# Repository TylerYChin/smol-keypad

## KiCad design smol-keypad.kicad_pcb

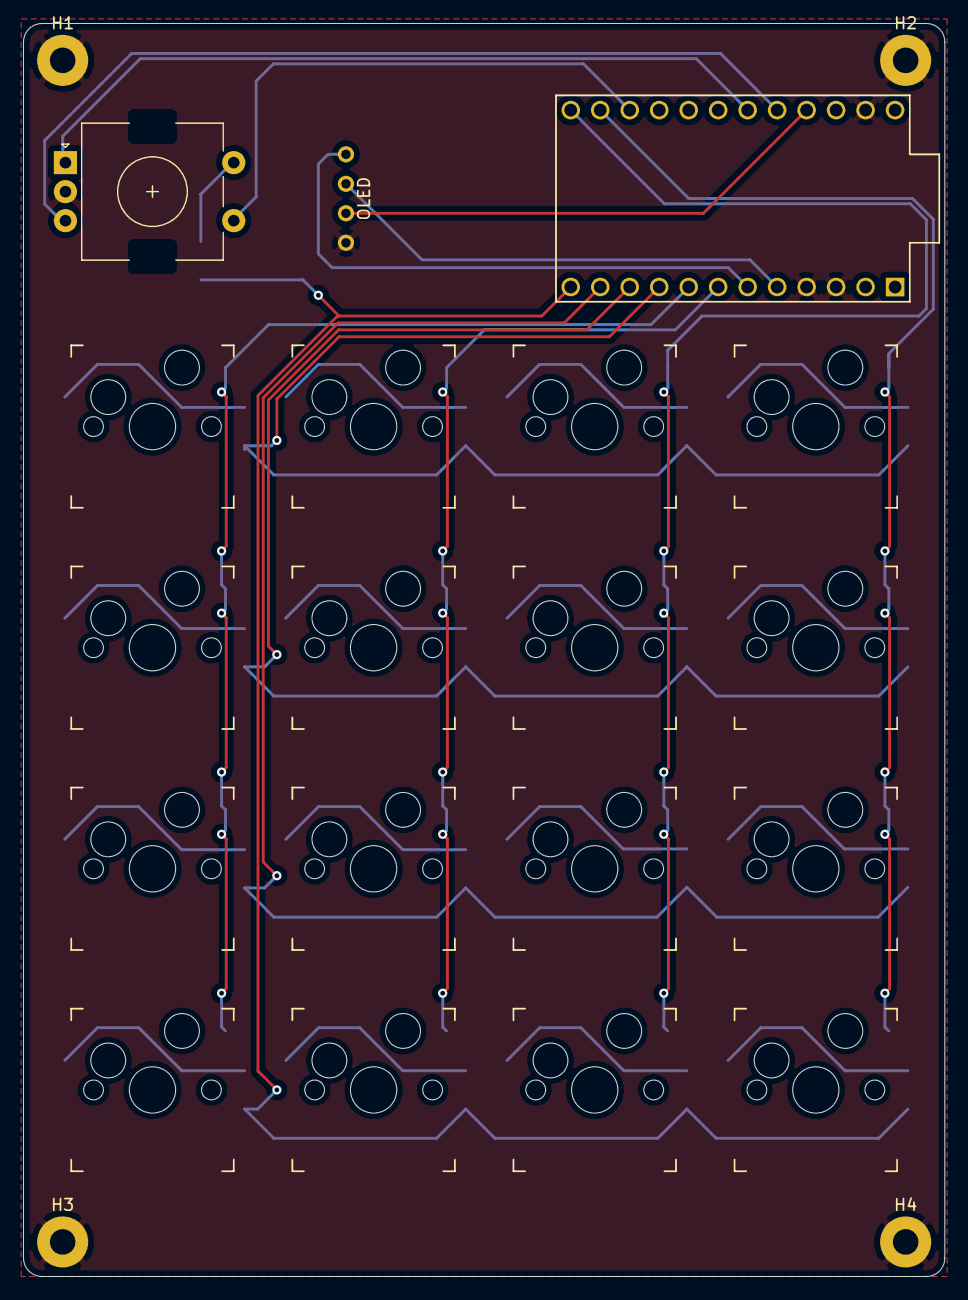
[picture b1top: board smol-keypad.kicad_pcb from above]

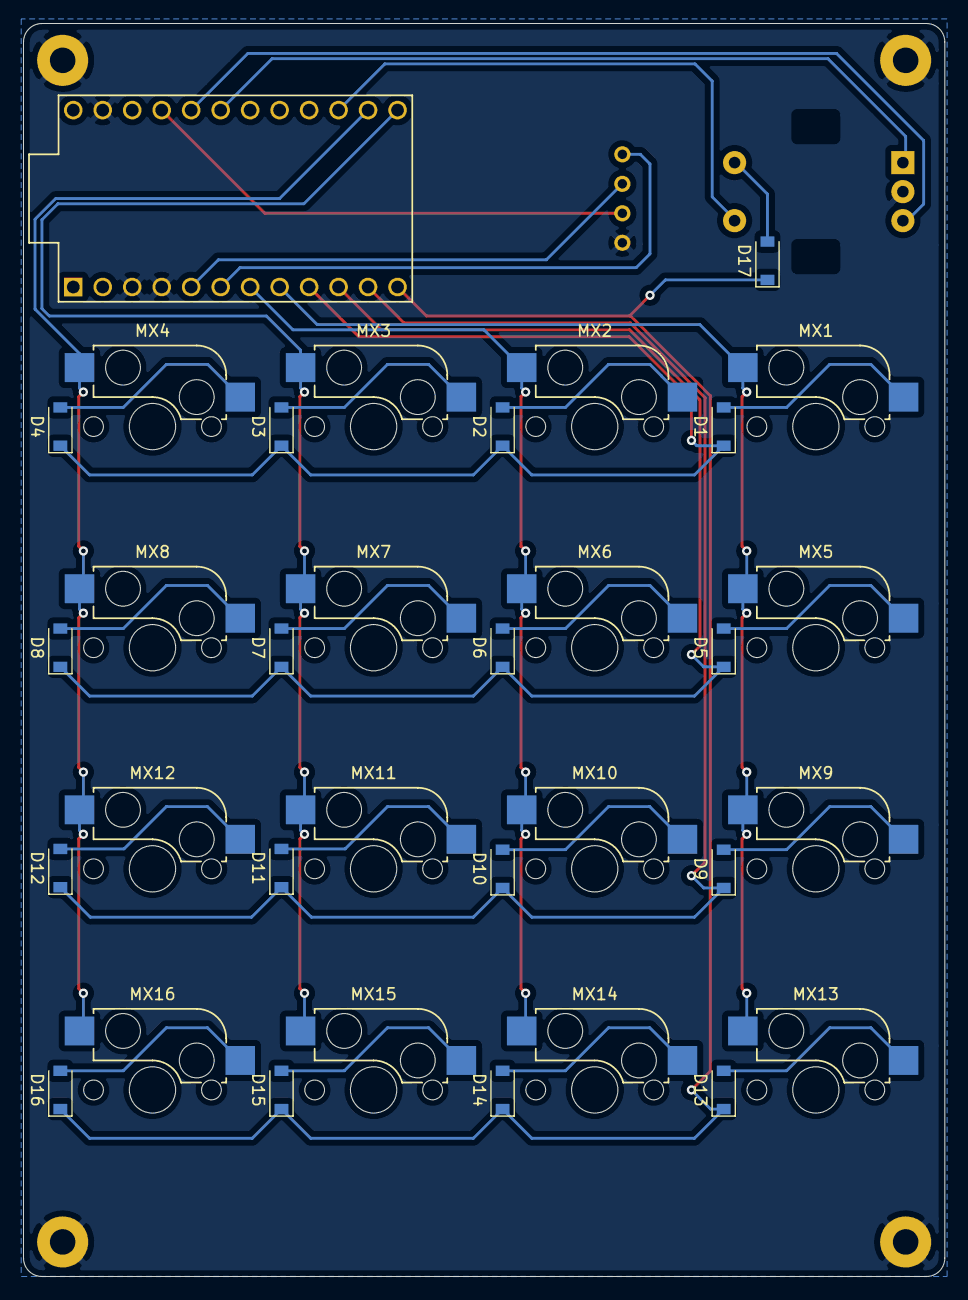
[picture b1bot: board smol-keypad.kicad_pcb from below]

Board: 2 copper layers, 79.4 x 107.9 mm, 40 parts (18 on the bottom side), 32 nets.

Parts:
D1, D2, D3, D4, D5, D6, D7, D8, D9, D10, D11, D12, D13, D14, D15, D16, D17: D_Small; D_SOD-123
H1, H2, H3, H4: MountingHole_Pad; MountingHole_2.2mm_M2_Pad
MX1, MX2, MX3, MX4, MX5, MX6, MX7, MX8, MX9, MX10, MX11, MX12, MX13, MX14, MX15, MX16: MX-NoLED; Kailh_socket_MX
OL1: OLED; OLED_v2
SW1: Rotary_Encoder_Switch; RotaryEncoder_EC11
U1: ProMicro

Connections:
/SCL: OL1.2, U1.5
/SDA: OL1.1, U1.6
/VCC: OL1.3, U1.21
/col0: MX1.1, MX5.1, MX9.1, MX13.1, U1.8
/col1: MX2.1, MX6.1, MX10.1, MX14.1, U1.7
/col2: MX3.1, MX7.1, MX11.1, MX15.1, U1.13
/col3: MX4.1, MX8.1, MX12.1, MX16.1, U1.14
/colRotEnc: SW1.S1, U1.15
/pinA: SW1.A, U1.19
/pinB: SW1.B, U1.20
/rotEnc: D17.2, SW1.S2
/row0: D1.1, D2.1, D3.1, D4.1, U1.9
/row1: D5.1, D6.1, D7.1, D8.1, U1.10
/row2: D9.1, D10.1, D11.1, D12.1, U1.11
/row3: D13.1, D14.1, D15.1, D16.1, D17.1, U1.12
GND: H1.1, H2.1, H3.1, H4.1, OL1.4, SW1.C, U1.3, U1.4, U1.23
unnamed: D1.2, MX1.2
unnamed: D2.2, MX2.2
unnamed: D3.2, MX3.2
unnamed: D4.2, MX4.2
unnamed: D5.2, MX5.2
unnamed: D6.2, MX6.2
unnamed: D7.2, MX7.2
unnamed: D8.2, MX8.2
unnamed: D9.2, MX9.2
unnamed: D10.2, MX10.2
unnamed: D11.2, MX11.2
unnamed: D12.2, MX12.2
unnamed: D13.2, MX13.2
unnamed: D14.2, MX14.2
unnamed: D15.2, MX15.2
unnamed: D16.2, MX16.2

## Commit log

2021-05-19 Add submodules
2021-05-19 base
2021-05-19 Create SparkFun-Kicad-Libraries
2021-05-19 test
2021-05-19 add joystick files
2021-05-19 add joystick submodule
2021-05-19 add joystick2
2021-05-19 6:23
2021-05-19 remove submodules from project
2021-05-19 remove unused submodule files
2021-05-19 add hotswap libraries
2021-05-20 night
2021-05-20 add rotary encoders
2021-05-20 add kbd library
2021-05-20 final
2021-05-22 final final
2021-06-02 update diode footprint
2021-06-02 add firmware files
